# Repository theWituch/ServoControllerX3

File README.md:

# SCX3
3 Axis **Open-Loop STEP/DIR Position Control** to **Closed-Loop +/-10V Speed Control** Interface

## About
The system is an interface between two systemically incompatible types of control - open loop STEP/DIR in which there is no feedback, because it is open, and closed loop +/- 10V in which the DIRECT feedback is in the form of the axis position from a linear encoder for a linear axis or rotary for rotary axes (e.g. rotary table).

## How it works

The open-loop CNC controller has no coupling, it only sends STEP/DIR signals and waits for the movement to be performed, e.g. by a stepper motor or servo drive with a STEP / DIR input. This solution is nice and cheap, but it brings with it problems such as the lack of feedback on whether the move was actually made.

Of course, it is possible to detect, for example, in self-drives, the lack of rotation of the motor shaft, but the rotation of the motor does not have to mean the axis shift (failure).

In addition, the entire kinematic chain, which has its efficiency, causes that the positioning from the motor axis is not accurately reflected at the end of the chain (on the machine table).

## Project assumptions

The assumptions for the system were such as to:
* fit on one board for three axes of the machine
* reduce noise on the analog outputs +/- 10V
* ensure internal distribution of the necessary voltages for the system (uC, outputs +/- 10V) and connected encoders from the power supply 12-24VDC
* add a readiness relay (not a safe output, only OK status signaling, as in the servers it was supposed to cooperate with)
* increase the uC computing power
* increase the capacity of the encoder inputs
* integrate the RS232 interface in the system
* and adjust the shape of the board to the format that allows it to be reasonably mounted, e.g. on a DIN rail.

## Progress

The project, due to the fact that while writing the firmware, I encountered a bug with the EEPROM memory built into the uC, it got stuck for a good two years.

Problem: https://www.microchip.com/forums/m1043135.aspx  
Solution: https://www.microchip.com/forums/FindPost/1064146

## Versions

See version description to get more detailed informations.

* [version 1.2.0](V1.2.0.md)
* [version 1.1.0](V1.1.0.md)
* [version 1.0.0](V1.0.0.md)

## License

Whole SCX3 project follow [CC-BY-NC-SA-4.0 license](https://creativecommons.org/licenses/by-nc-sa/4.0/). Thus, project is freely available for academic purpose or individual research, but restricted for commecial use.

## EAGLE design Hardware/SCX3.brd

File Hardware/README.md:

# SCX3 Hardware
3 Axis **Open-Loop STEP/DIR Position Control** to **Closed-Loop +/-10V Speed Control** Interface - Hardware

## About

The hardware for the SCX3 controller was developed using the EAGLE 7.7.0 environment.

## Status

The project has not been developed for a long time and the content of the repository has not been checked. Therefore, there is no guarantee that the project files will generate a PCB without any additional steps.

Additionally, this hardware version (1.2.0) has not been tested on the built prototype.

The only version tested on a prototype is 1.0.0 - which contained bugs that were fixed in later versions.

## License

SCX3 Hardware follow [CC-BY-NC-SA-4.0 license](LICENSE). Thus, those compounds are freely available for academic purpose or individual research, but restricted for commecial use.

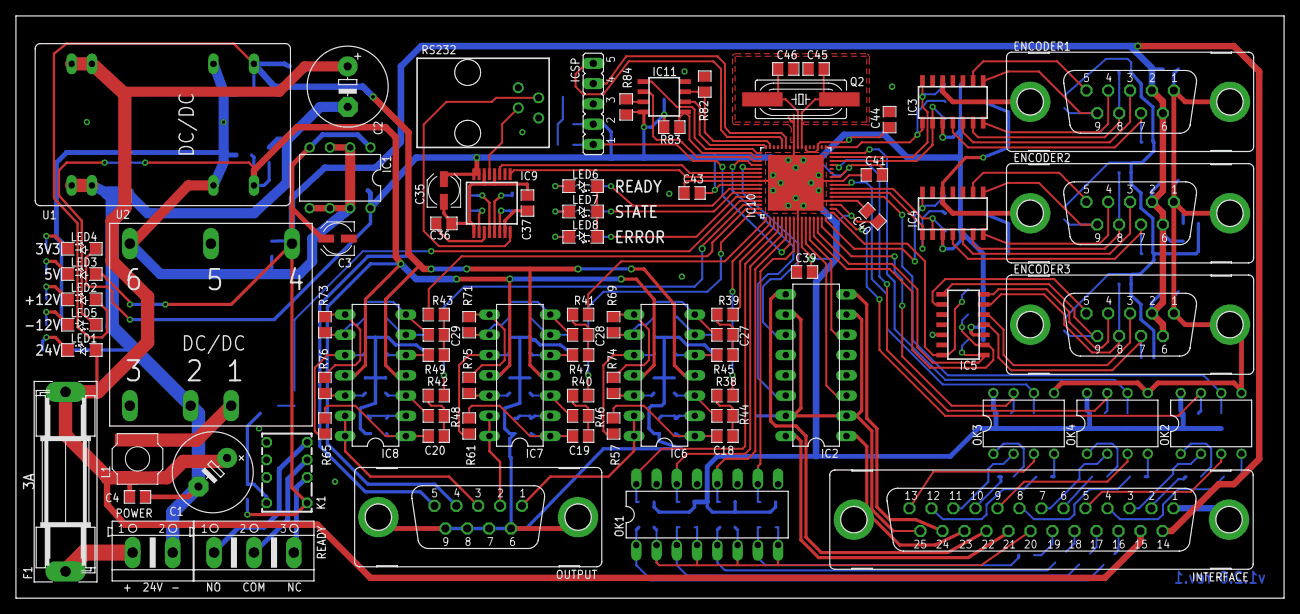
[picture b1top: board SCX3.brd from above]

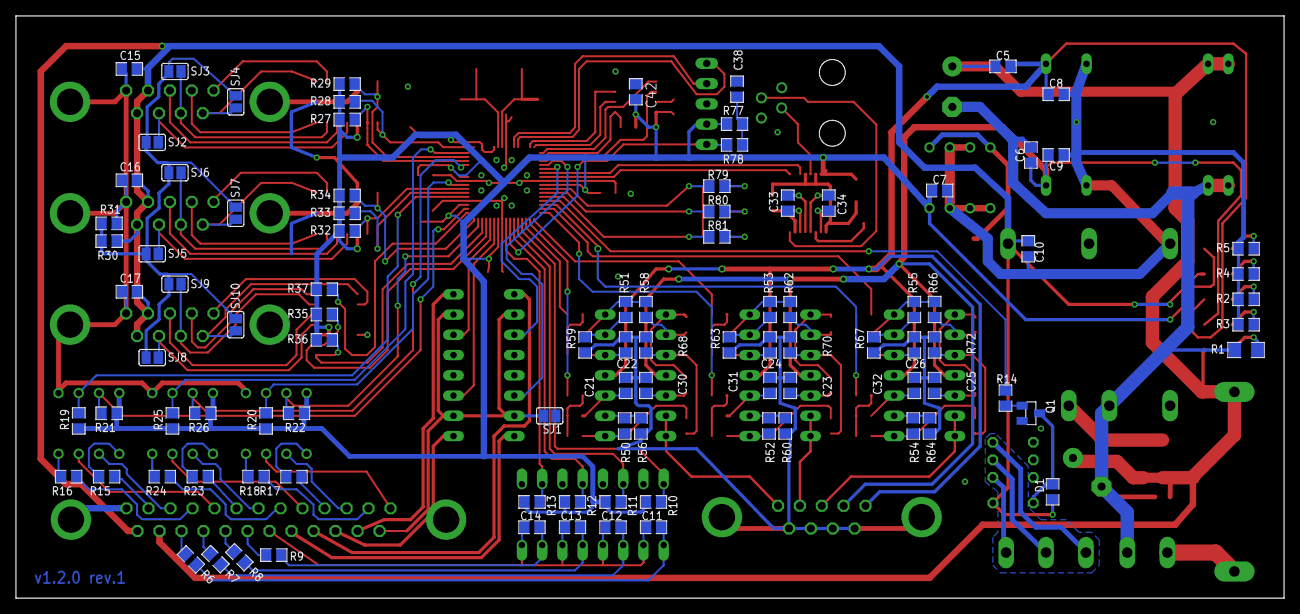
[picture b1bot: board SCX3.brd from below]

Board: 2 copper layers, 159.0 x 73.0 mm, 180 parts (98 on the bottom side), 167 nets.

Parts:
C1: 330uF; E5-10,5
C2: 220uF; E5-10,5
C3: 10uF; UD-4X5,8_NICHICON
C4, C8, C9: 1uF; C0805
C5, C6: 1nF/1KV; C0805
C7, C10, C15, C16, C17: 10uF; C0805
C11, C12, C13, C14, C33, C34, C36, C37, C38, C39, C40, C41, C42, C43, C44: 100n; C0805
C18, C19, C20, C27, C28, C29: 10n; C0805
C21, C22, C23, C24, C25, C26, C30, C31, C32: 33n; C0805
C35: 100n; UD-4X5,8_NICHICON
C45, C46: 27p; C0805
D1: 1N4148SMD-0805; D0805
ENCODER1, ENCODER2, ENCODER3: F09VP
F1: 3A; SH22,5
IC1: MAX604; DIL08
IC2: ULN2074BN; DIL16
IC3, IC4, IC5: LM339D; SO14
IC6, IC7, IC8: LM324N; DIL14
IC9: MAX3221CAE; SSOP16
IC10: PIC32MK1024MCF064; QFN64-9X9
IC11: M95040; SO8
ICSP: ICSP; JP5
INTERFACE: F25VP
K1: G6K-2P-Y
L1: 4,7uH; DJNR6028
LED1: LED 24V; SML1206
LED2: LED +12V; SML1206
LED3: LED 5V; SML1206
LED4: LED 3V3; SML1206
LED5: LED -12V; SML1206
LED6: LED READY; SML1206
LED7: LED STATE; SML1206
LED8: LED ERROR; SML1206
OK1: LTV844; DIL16
OK2, OK3, OK4: TLP2662F; DIL08
OUTPUT: F09VP
POWER: 12/24V_CON; AK500/2
Q1: BC848SMD; SOT23
Q2: 20MHz 18pF; SM49
R1: 2K2; R1206
R2, R3, R6, R7, R8, R9, R30, R78: 1K; R0805
R4: 330; R0805
R5, R79, R80, R81: 100; R0805
R10, R11, R12, R13, R14, R19, R20, R21, R22, R25, R26, R27, R28, R29, R32, R33, R34, R35, R36, R37, R82, R83, R84: 4K7; R0805
R15, R16, R17, R18, R23, R24, R31: 470; R0805
R38, R39, R40, R41, R42, R43, R50, R51, R52, R53, R54, R55, R57, R58, R61, R62, R65, R66, R74, R75, R76: 22K; R0805
R44, R45, R46, R47, R48, R49, R77: 10K; R0805
R56, R59, R60, R63, R64, R67, R68, R69, R70, R71, R72, R73: 47K; R0805
READY: READY; AK500/3
RS232: RJ-9
SJ1, SJ2, SJ3, SJ4, SJ5, SJ6, SJ7, SJ8, SJ9, SJ10: SJ
U1: AM6T-2412D-NZ; AM6T
U2: AM10CW-2405S-NZ; AM10CW-NZ

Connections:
3V3: C7.1, C35.+, C39.2, C40.1, C41.2, C42.2, C43.2, C44.1, IC1.8, IC3.3, IC4.3, IC5.3, IC9.15, IC9.16, IC10.10, IC10.19, IC10.26, IC10.35, IC10.38, IC10.57, IC11.8, ICSP.2, LED4.A, OK2.8, OK3.8, OK4.8, R10.2, R11.2, R12.2, R13.2, R19.2, R20.2, R21.2, R22.2, R25.2, R26.2, R27.2, R28.2, R29.2, R32.2, R33.2, R34.2, R35.2, R36.2, R37.2, R77.2, R83.1, R84.1
5V: C3.+, C10.1, C15.2, C16.2, C17.2, D1.2, ENCODER1.2, ENCODER1.6, ENCODER2.2, ENCODER2.6, ENCODER3.2, ENCODER3.6, IC1.1, IC1.4, INTERFACE.14, K1.1, LED3.A, R30.2, U2.4
24V: C1.+, C2.+, C4.1, C5.1, F1.2, INTERFACE.15, L1.A, LED1.A, U1.22, U1.23
24VGND: C1.-, C2.-, C4.2, C6.2, POWER.2, R1.2, U1.2, U1.3, U2.2
!HOLD: IC11.7, R84.2
!MCLR: IC10.7, ICSP.1, R78.2
!MSS: IC10.50, IC11.1, R83.2
!MWP: IC10.47, IC11.3, R82.2
+12V: C5.2, C8.1, IC6.4, IC7.4, IC8.4, LED2.A, OUTPUT.5, U1.14
-12V: C6.1, C9.2, IC6.11, IC7.11, IC8.11, LED5.C, OUTPUT.4, U1.11
CH1_A+: ENCODER1.3, IC3.5
CH1_A-: ENCODER1.7, IC3.4, SJ2.2
CH1_B+: ENCODER1.4, IC3.7
CH1_B-: ENCODER1.8, IC3.6, SJ3.2
CH1_CMD: IC6.13, IC6.14, OUTPUT.1
CH1_DIR: IC10.21, OK2.6, R19.1
CH1_DIR_H: INTERFACE.4, R16.1
CH1_DIR_L: INTERFACE.5, OK2.3
CH1_H: IC10.2, R38.1
CH1_I+: ENCODER1.5, IC3.9
CH1_I-: ENCODER1.9, IC3.8, SJ4.2
CH1_L: IC10.3, R39.1
CH1_QE_A: IC3.2, IC10.30, R27.1
CH1_QE_B: IC3.1, IC10.33, R28.1
CH1_QE_I: IC3.14, IC10.31, R29.1
CH1_STEP: IC10.18, OK2.7, R21.1
CH1_STEP_H: INTERFACE.2, R15.1
CH1_STEP_L: INTERFACE.3, OK2.2
CH2_A+: ENCODER2.3, IC4.5
CH2_A-: ENCODER2.7, IC4.4, SJ5.2
CH2_B+: ENCODER2.4, IC4.7
CH2_B-: ENCODER2.8, IC4.6, SJ6.2
CH2_CMD: IC7.13, IC7.14, OUTPUT.2
CH2_DIR: IC10.32, OK4.6, R25.1
CH2_DIR_H: INTERFACE.8, R24.1
CH2_DIR_L: INTERFACE.9, OK4.3
CH2_H: IC10.64, R40.1
CH2_I+: ENCODER2.5, IC4.9
CH2_I-: ENCODER2.9, IC4.8, SJ7.2
CH2_L: IC10.1, R41.1
CH2_QE_A: IC4.2, IC10.23, R32.1
CH2_QE_B: IC4.1, IC10.22, R33.1
CH2_QE_I: IC4.14, IC10.16, R34.1
CH2_STEP: IC10.29, OK4.7, R26.1
CH2_STEP_H: INTERFACE.6, R23.1
CH2_STEP_L: INTERFACE.7, OK4.2
CH3_A+: ENCODER3.3, IC5.5
CH3_A-: ENCODER3.7, IC5.4, SJ8.2
CH3_B+: ENCODER3.4, IC5.7
CH3_B-: ENCODER3.8, IC5.6, SJ9.2
CH3_CMD: IC8.13, IC8.14, OUTPUT.3
CH3_DIR: IC10.24, OK3.6, R20.1
CH3_DIR_H: INTERFACE.12, R18.1
CH3_DIR_L: INTERFACE.13, OK3.3
CH3_H: IC10.62, R42.1
CH3_I+: ENCODER3.5, IC5.9
CH3_I-: ENCODER3.9, IC5.8, SJ10.2
CH3_L: IC10.63, R43.1
CH3_QE_A: IC5.2, IC10.13, R35.1
CH3_QE_B: IC5.1, IC10.14, R36.1
CH3_QE_I: IC5.14, IC10.17, R37.1
CH3_STEP: IC10.15, OK3.7, R22.1
CH3_STEP_H: INTERFACE.10, R17.1
CH3_STEP_L: INTERFACE.11, OK3.2
DI1: IC10.4, OK1.16, R10.1
DI1_CON: INTERFACE.16, R6.1
DI2: IC10.5, OK1.14, R11.1
DI2_CON: INTERFACE.17, R7.1
DI3: IC10.6, OK1.12, R12.1
DI3_CON: INTERFACE.18, R8.1
DI4: IC10.8, OK1.10, R13.1
DI4_CON: INTERFACE.19, R9.1
DI_COM_CON: C11.2, C12.2, C13.2, C14.2, INTERFACE.20, OK1.2, OK1.4, OK1.6, OK1.8
DO1: IC2.14, IC10.52
DO1H_CON: D1.1, K1.8, Q1.3
DO1_CON: IC2.16, INTERFACE.21
DO2: IC2.11, IC10.53
DO2_CON: IC2.9, INTERFACE.22
DO3: IC2.3, IC10.11
DO3_CON: IC2.1, INTERFACE.23
DO4: IC2.6, IC10.12
DO4_CON: IC2.8, INTERFACE.24
DO_COM_CON: IC2.2, IC2.7, IC2.10, IC2.15, INTERFACE.25, SJ1.2
GND: C3.-, C7.2, C8.2, C9.1, C10.2, C15.1, C16.1, C17.1, C21.1, C22.2, C23.1, C24.2, C25.1, C26.2, C30.2, C31.2, C32.2, C35.-, C36.2, C37.2, C38.1, C39.1, C40.2, C41.1, C42.1, C43.1, C44.2, C45.1, C46.1, ENCODER1.1, ENCODER1.G1, ENCODER1.G2, ENCODER2.1, ENCODER2.G1, ENCODER2.G2, ENCODER3.1, ENCODER3.G1, ENCODER3.G2, IC1.2, IC1.3, IC1.5, IC1.6, IC1.7, IC2.4, IC2.5, IC2.12, IC2.13, IC3.12, IC4.12, IC5.12, IC9.1, IC9.12, IC9.14, IC10.9, IC10.20, IC10.25, IC10.41, IC10.56, IC10.EXP, IC11.4, ICSP.3, INTERFACE.1, INTERFACE.G1, INTERFACE.G2, LED6.C, LED7.C, LED8.C, OK1.9, OK1.11, OK1.13, OK1.15, OK2.5, OK3.5, OK4.5, OUTPUT.6, OUTPUT.7, OUTPUT.8, OUTPUT.9, OUTPUT.G1, OUTPUT.G2, Q1.2, R2.2, R3.2, R4.2, R5.2, R31.1, R56.2, R59.1, R60.2, R63.1, R64.2, R67.1, R68.1, R70.1, R72.1, R82.1, RS232.1, RS232.4, SJ1.1, U1.9, U1.16, U2.6
LED_ERROR: IC10.60, R81.1
LED_READY: IC10.58, R79.1
LED_STATE: IC10.59, R80.1
MSCK: IC10.51, IC11.6
MSDI: IC10.48, IC11.2
MSDO: IC10.49, IC11.5
unnamed: IC6.6, R51.1, R59.2
unnamed: IC6.2, R50.2, R56.1
unnamed: LED1.C, R1.1
unnamed: L1.B, U2.1
unnamed: C18.1, IC6.1, R50.1, R57.2
unnamed: C21.2, IC6.3, R44.2
unnamed: C18.2, R38.2, R44.1
unnamed: C30.1, IC6.12, R74.2
unnamed: IC6.8, R69.2, R74.1
unnamed: IC6.9, R58.1, R69.1
unnamed: C27.2, IC6.7, R51.2, R58.2
unnamed: F1.1, POWER.1
unnamed: C22.1, IC6.5, R45.2
unnamed: C27.1, R39.2, R45.1
unnamed: IC6.10, R57.1, R68.2
unnamed: OK4.4, R24.2
unnamed: OK4.1, R23.2
unnamed: OK3.4, R18.2
unnamed: OK3.1, R17.2
unnamed: IC7.6, R53.1, R63.2
unnamed: IC7.2, R52.2, R60.1
unnamed: C19.1, IC7.1, R52.1, R61.2
unnamed: C23.2, IC7.3, R46.2
unnamed: C19.2, R40.2, R46.1
unnamed: C31.1, IC7.12, R75.2
unnamed: IC7.8, R71.2, R75.1
unnamed: IC7.9, R62.1, R71.1
unnamed: C28.2, IC7.7, R53.2, R62.2
unnamed: C24.1, IC7.5, R47.2
unnamed: C28.1, R41.2, R47.1
unnamed: IC7.10, R61.1, R70.2
unnamed: IC8.6, R55.1, R67.2
unnamed: IC8.2, R54.2, R64.1
unnamed: C20.1, IC8.1, R54.1, R65.2
unnamed: C25.2, IC8.3, R48.2
unnamed: C20.2, R42.2, R48.1
unnamed: C32.1, IC8.12, R76.2
unnamed: IC8.8, R73.2, R76.1
unnamed: IC8.9, R66.1, R73.1
unnamed: C29.2, IC8.7, R55.2, R66.2
unnamed: C26.1, IC8.5, R49.2
unnamed: C29.1, R43.2, R49.1
unnamed: IC8.10, R65.1, R72.2
unnamed: LED6.A, R79.2
unnamed: LED7.A, R80.2
unnamed: LED8.A, R81.2
unnamed: C34.2, IC9.4
unnamed: C34.1, IC9.2
unnamed: C33.2, IC9.6
unnamed: C33.1, IC9.5
unnamed: C36.1, IC9.3
unnamed: C37.1, IC9.7
unnamed: C12.1, OK1.3, R7.2
unnamed: LED2.C, R2.1
unnamed: LED3.C, R4.1
unnamed: C38.2, R77.1, R78.1
unnamed: Q1.1, R14.2
unnamed: C13.1, OK1.5, R8.2
unnamed: C14.1, OK1.7, R9.2
unnamed: C11.1, OK1.1, R6.2
unnamed: OK2.4, R16.2
unnamed: OK2.1, R15.2
unnamed: LED4.C, R5.1
unnamed: LED5.A, R3.1
OSC1I: C45.2, IC10.39, Q2.2
OSC1O: C46.2, IC10.40, Q2.1
PGEC: IC10.44, ICSP.5
PGED: IC10.43, ICSP.4
REF: R30.1, R31.2, SJ2.1, SJ3.1, SJ4.1, SJ5.1, SJ6.1, SJ7.1, SJ8.1, SJ9.1, SJ10.1
RO1: IC10.61, R14.1
RO1_COM_CON: K1.3, READY.2
RO1_NC_CON: K1.2, READY.3
RO1_NO_CON: K1.4, READY.1
RS232_RX: IC9.8, RS232.2
RS232_TX: IC9.13, RS232.3
UART_RX: IC9.9, IC10.55
UART_TX: IC9.11, IC10.54

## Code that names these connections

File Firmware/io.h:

#define DI1             ~PORTGbits.RG6
#define DI2             ~PORTGbits.RG7
#define DI3             ~PORTGbits.RG8
#define DI4             ~PORTGbits.RG9

#define DO1             LATCbits.LATC8
#define DO2             LATDbits.LATD5
#define DO3             LATAbits.LATA12
#define DO4             LATAbits.LATA11

#define RO1             LATBbits.LATB11

#define LED_READY       LATFbits.LATF0
#define LED_STATE       LATFbits.LATF1
#define LED_ERROR       LATBbits.LATB10

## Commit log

2022-01-07 First release 1.0.0
2022-01-07 Release 1.1.0
2022-01-07 Release 1.2.0
2022-01-07 Add more detailed informations about project
2022-01-07 [BROKEN] Rotated encoder 3 gate transoptor (IC5)
    Only for the purpose of containing the concept of positioning the elements
2022-03-04 Set theme jekyll-theme-dinky
2022-03-04 Set theme jekyll-theme-minimal
2022-03-04 Set theme jekyll-theme-hacker
2022-03-04 Set theme jekyll-theme-slate
